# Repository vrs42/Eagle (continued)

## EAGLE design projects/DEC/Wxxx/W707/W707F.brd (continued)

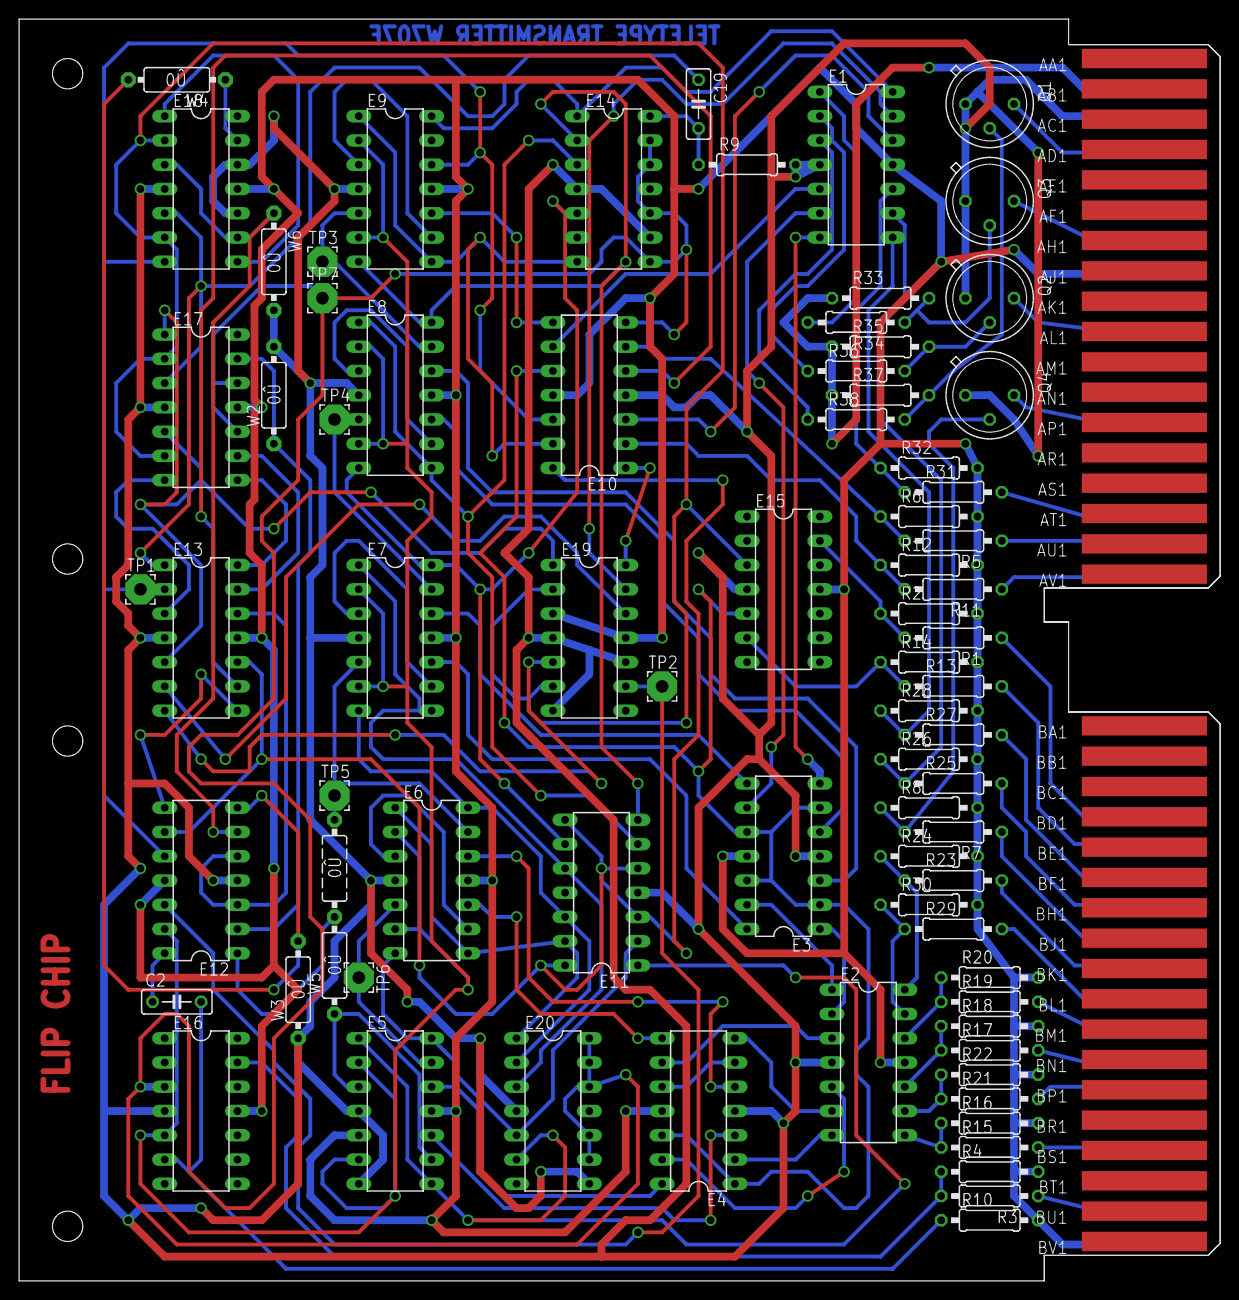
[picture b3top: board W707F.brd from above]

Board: 3 copper layers, 125.7 x 132.1 mm, 79 parts (0 on the bottom side), 110 nets.

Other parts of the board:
U$3: FLIPCHIP

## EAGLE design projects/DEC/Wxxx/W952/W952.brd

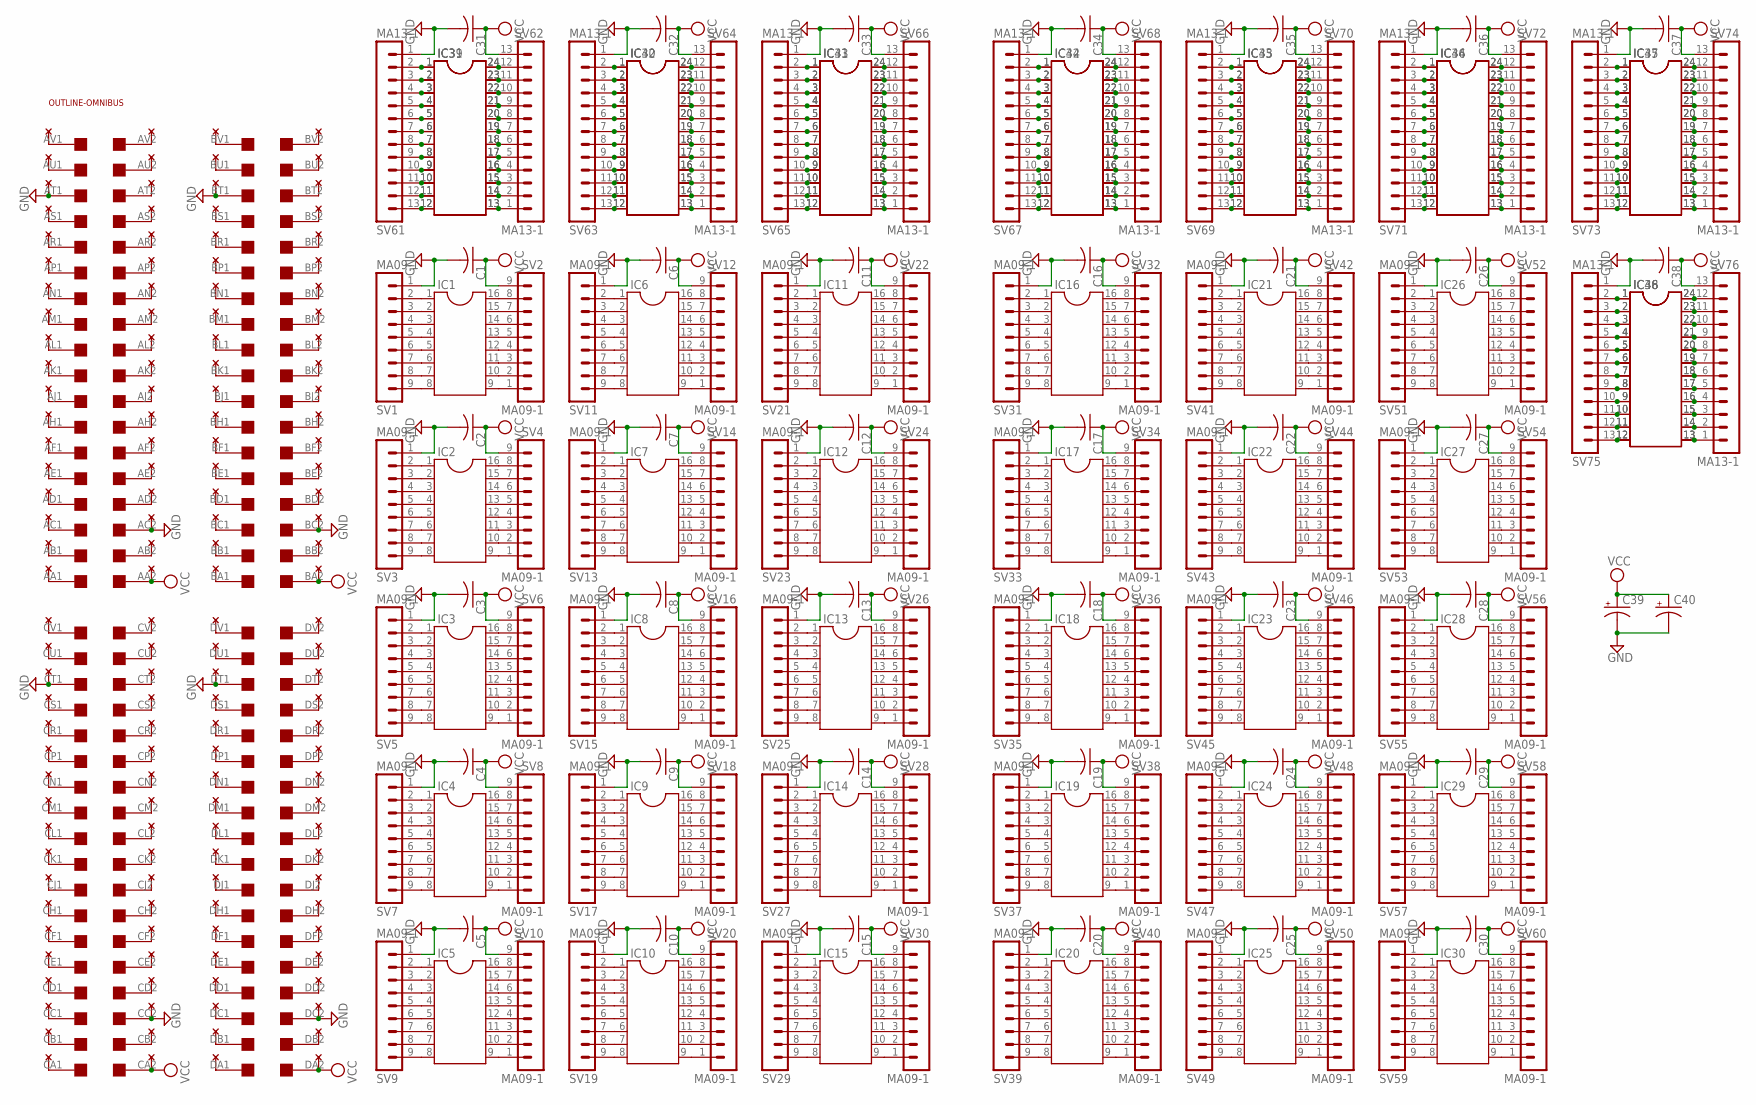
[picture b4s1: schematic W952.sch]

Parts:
C1, C2, C3, C4, C5, C6, C7, C8, C9, C10, C11, C12, C13, C14, C15, C16, C17, C18, C19, C20, C21, C22, C23, C24, C25, C26, C27, C28, C29, C30, C31, C32, C33, C34, C35, C36, C37, C38: C-US075-032X103; C075-032X103
C39, C40: CPOL-USE15-5AXIAL; E15-5
IC1, IC2, IC3, IC4, IC5, IC6, IC7, IC8, IC9, IC10, IC11, IC12, IC13, IC14, IC15, IC16, IC17, IC18, IC19, IC20, IC21, IC22, IC23, IC24, IC25, IC26, IC27, IC28, IC29, IC30: DIL16S; SOCKET-16
IC31, IC32, IC33, IC34, IC35, IC36, IC37, IC38: DIL24-6
IC39, IC40, IC41, IC42, IC43, IC44, IC45, IC46: DIL24-3
SV1, SV2, SV3, SV4, SV5, SV6, SV7, SV8, SV9, SV10, SV11, SV12, SV13, SV14, SV15, SV16, SV17, SV18, SV19, SV20, SV21, SV22, SV23, SV24, SV25, SV26, SV27, SV28, SV29, SV30, SV31, SV32, SV33, SV34, SV35, SV36, SV37, SV38, SV39, SV40, SV41, SV42, SV43, SV44, SV45, SV46, SV47, SV48, SV49, SV50, SV51, SV52, SV53, SV54, SV55, SV56, SV57, SV58, SV59, SV60: MA09-1
SV61, SV62, SV63, SV64, SV65, SV66, SV67, SV68, SV69, SV70, SV71, SV72, SV73, SV74, SV75, SV76: MA13-1
U$1: QUAD; EDGE-CON8
U$2, U$3, U$4, U$5: THRU-HOLE2W; THRU-HOLE2
U$8: OUTLINE-OMNIBUS; OMNIBUS

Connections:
GND: C1.2, C2.2, C3.2, C4.2, C5.2, C6.2, C7.2, C8.2, C9.2, C10.2, C11.2, C12.2, C13.2, C14.2, C15.2, C16.2, C17.2, C18.2, C19.2, C20.2, C21.2, C22.2, C23.2, C24.2, C25.2, C26.2, C27.2, C28.2, C29.2, C30.2, C31.2, C32.2, C33.2, C34.2, C35.2, C36.2, C37.2, C38.2, C39.-, C40.-, SV1.1, SV3.1, SV5.1, SV7.1, SV9.1, SV11.1, SV13.1, SV15.1, SV17.1, SV19.1, SV21.1, SV23.1, SV25.1, SV27.1, SV29.1, SV31.1, SV33.1, SV35.1, SV37.1, SV39.1, SV41.1, SV43.1, SV45.1, SV47.1, SV49.1, SV51.1, SV53.1, SV55.1, SV57.1, SV59.1, SV61.1, SV63.1, SV65.1, SV67.1, SV69.1, SV71.1, SV73.1, SV75.1, U$1.AC2, U$1.AT1, U$1.BC2, U$1.BT1, U$1.CC2, U$1.CT1, U$1.DC2, U$1.DT1, U$2.C1, U$2.T2, U$3.C1, U$3.T2, U$4.C1, U$4.T2, U$5.C1, U$5.T2
unnamed: U$1.AK1, U$2.K2
unnamed: U$1.AJ1, U$2.J2
unnamed: U$1.AH1, U$2.H2
unnamed: U$1.AL1, U$2.L2
unnamed: U$1.AM1, U$2.M2
unnamed: U$1.AN1, U$2.N2
unnamed: U$1.AP1, U$2.P2
unnamed: U$1.AF1, U$2.F2
unnamed: U$1.AE1, U$2.E2
unnamed: U$1.AD1, U$2.D2
unnamed: U$1.AC1, U$2.C2
unnamed: U$1.AR1, U$2.R2
unnamed: U$1.AS1, U$2.S2
unnamed: U$1.AB1, U$2.B2
unnamed: U$1.AA1, U$2.A2
unnamed: U$1.AU1, U$2.U2
unnamed: U$1.AV1, U$2.V2
unnamed: U$1.AV2, U$2.V1
unnamed: U$1.AU2, U$2.U1
unnamed: U$1.AT2, U$2.T1
unnamed: U$1.AS2, U$2.S1
unnamed: U$1.AR2, U$2.R1
unnamed: U$1.AP2, U$2.P1
unnamed: U$1.AN2, U$2.N1
unnamed: U$1.AM2, U$2.M1
unnamed: U$1.AL2, U$2.L1
unnamed: U$1.AK2, U$2.K1
unnamed: U$1.AJ2, U$2.J1
unnamed: U$1.AH2, U$2.H1
unnamed: U$1.AF2, U$2.F1
unnamed: U$1.AE2, U$2.E1
unnamed: U$1.AD2, U$2.D1
unnamed: U$1.AB2, U$2.B1
unnamed: U$1.BV1, U$3.V2
unnamed: U$1.BU1, U$3.U2
unnamed: U$1.BS1, U$3.S2
unnamed: U$1.BR1, U$3.R2
unnamed: U$1.BP1, U$3.P2
unnamed: U$1.BN1, U$3.N2
unnamed: U$1.BM1, U$3.M2
unnamed: U$1.BL1, U$3.L2
unnamed: U$1.BK1, U$3.K2
unnamed: U$1.BJ1, U$3.J2
unnamed: U$1.BH1, U$3.H2
unnamed: U$1.BF1, U$3.F2
unnamed: U$1.BE1, U$3.E2
unnamed: U$1.BD1, U$3.D2
unnamed: U$1.BC1, U$3.C2
unnamed: U$1.BB1, U$3.B2
unnamed: U$1.BA1, U$3.A2
unnamed: U$1.BV2, U$3.V1
unnamed: U$1.BU2, U$3.U1
unnamed: U$1.BT2, U$3.T1
unnamed: U$1.BS2, U$3.S1
unnamed: U$1.BR2, U$3.R1
unnamed: U$1.BP2, U$3.P1
unnamed: U$1.BN2, U$3.N1
unnamed: U$1.BM2, U$3.M1
unnamed: U$1.BL2, U$3.L1
unnamed: U$1.BK2, U$3.K1
unnamed: U$1.BJ2, U$3.J1
unnamed: U$1.BH2, U$3.H1
unnamed: U$1.BF2, U$3.F1
unnamed: U$1.BE2, U$3.E1
unnamed: U$1.BD2, U$3.D1
unnamed: U$1.BB2, U$3.B1
unnamed: U$1.CV1, U$4.V2
unnamed: U$1.CU1, U$4.U2
unnamed: U$1.CS1, U$4.S2
unnamed: U$1.CR1, U$4.R2
unnamed: U$1.CP1, U$4.P2
unnamed: U$1.CN1, U$4.N2
unnamed: U$1.CM1, U$4.M2
unnamed: U$1.CL1, U$4.L2
unnamed: U$1.CK1, U$4.K2
unnamed: U$1.CJ1, U$4.J2
unnamed: U$1.CH1, U$4.H2
unnamed: U$1.CF1, U$4.F2
unnamed: U$1.CE1, U$4.E2
unnamed: U$1.CD1, U$4.D2
unnamed: U$1.CC1, U$4.C2
unnamed: U$1.CB1, U$4.B2
unnamed: U$1.CA1, U$4.A2
unnamed: U$1.CV2, U$4.V1
unnamed: U$1.CU2, U$4.U1
unnamed: U$1.CT2, U$4.T1
unnamed: U$1.CS2, U$4.S1
unnamed: U$1.CR2, U$4.R1
unnamed: U$1.CP2, U$4.P1
unnamed: U$1.CN2, U$4.N1
unnamed: U$1.CM2, U$4.M1
unnamed: U$1.CL2, U$4.L1
unnamed: U$1.CK2, U$4.K1
unnamed: U$1.CJ2, U$4.J1
unnamed: U$1.CH2, U$4.H1
unnamed: U$1.CF2, U$4.F1
unnamed: U$1.CE2, U$4.E1
unnamed: U$1.CD2, U$4.D1
unnamed: U$1.CB2, U$4.B1
unnamed: U$1.DV1, U$5.V2
unnamed: U$1.DU1, U$5.U2
unnamed: U$1.DS1, U$5.S2
unnamed: U$1.DR1, U$5.R2
unnamed: U$1.DP1, U$5.P2
unnamed: U$1.DN1, U$5.N2
unnamed: U$1.DM1, U$5.M2
unnamed: U$1.DL1, U$5.L2
unnamed: U$1.DK1, U$5.K2
unnamed: U$1.DJ1, U$5.J2
unnamed: U$1.DH1, U$5.H2
unnamed: U$1.DF1, U$5.F2
unnamed: U$1.DE1, U$5.E2
unnamed: U$1.DD1, U$5.D2
unnamed: U$1.DC1, U$5.C2
unnamed: U$1.DB1, U$5.B2
unnamed: U$1.DA1, U$5.A2
unnamed: U$1.DV2, U$5.V1
unnamed: U$1.DU2, U$5.U1
unnamed: U$1.DT2, U$5.T1
unnamed: U$1.DS2, U$5.S1
unnamed: U$1.DR2, U$5.R1
unnamed: U$1.DP2, U$5.P1
unnamed: U$1.DN2, U$5.N1
unnamed: U$1.DM2, U$5.M1
unnamed: U$1.DL2, U$5.L1
unnamed: U$1.DK2, U$5.K1
unnamed: U$1.DJ2, U$5.J1
unnamed: U$1.DH2, U$5.H1
unnamed: U$1.DF2, U$5.F1
unnamed: U$1.DE2, U$5.E1
unnamed: U$1.DD2, U$5.D1
unnamed: U$1.DB2, U$5.B1
unnamed: IC1.1, SV1.2
unnamed: IC1.2, SV1.3
unnamed: IC1.3, SV1.4
unnamed: IC1.4, SV1.5
unnamed: IC1.5, SV1.6
unnamed: IC1.6, SV1.7
unnamed: IC1.7, SV1.8
unnamed: IC1.8, SV1.9
unnamed: IC1.9, SV2.1
unnamed: IC1.10, SV2.2
unnamed: IC1.11, SV2.3
unnamed: IC1.12, SV2.4
unnamed: IC1.13, SV2.5
unnamed: IC1.14, SV2.6
unnamed: IC1.15, SV2.7
unnamed: IC1.16, SV2.8
unnamed: IC2.1, SV3.2
unnamed: IC2.2, SV3.3
unnamed: IC2.3, SV3.4
unnamed: IC2.4, SV3.5
unnamed: IC2.5, SV3.6
unnamed: IC2.6, SV3.7
unnamed: IC2.7, SV3.8
unnamed: IC2.8, SV3.9
unnamed: IC2.9, SV4.1
unnamed: IC2.10, SV4.2
unnamed: IC2.11, SV4.3
unnamed: IC2.12, SV4.4
unnamed: IC2.13, SV4.5
unnamed: IC2.14, SV4.6
unnamed: IC2.15, SV4.7
unnamed: IC2.16, SV4.8
unnamed: IC3.1, SV5.2
unnamed: IC3.2, SV5.3
unnamed: IC3.3, SV5.4
unnamed: IC3.4, SV5.5
unnamed: IC3.5, SV5.6
unnamed: IC3.6, SV5.7
unnamed: IC3.7, SV5.8
unnamed: IC3.8, SV5.9
unnamed: IC3.9, SV6.1
unnamed: IC3.10, SV6.2
unnamed: IC3.11, SV6.3
unnamed: IC3.12, SV6.4
unnamed: IC3.13, SV6.5
unnamed: IC3.14, SV6.6
unnamed: IC3.15, SV6.7
unnamed: IC3.16, SV6.8
unnamed: IC4.1, SV7.2
unnamed: IC4.2, SV7.3
unnamed: IC4.3, SV7.4
unnamed: IC4.4, SV7.5
unnamed: IC4.5, SV7.6
unnamed: IC4.6, SV7.7
unnamed: IC4.7, SV7.8
unnamed: IC4.8, SV7.9
unnamed: IC4.9, SV8.1
unnamed: IC4.10, SV8.2
unnamed: IC4.11, SV8.3
unnamed: IC4.12, SV8.4
unnamed: IC4.13, SV8.5
unnamed: IC4.14, SV8.6
unnamed: IC4.15, SV8.7
unnamed: IC4.16, SV8.8
unnamed: IC5.1, SV9.2
unnamed: IC5.2, SV9.3
unnamed: IC5.3, SV9.4
unnamed: IC5.4, SV9.5
unnamed: IC5.5, SV9.6
unnamed: IC5.6, SV9.7
unnamed: IC5.7, SV9.8
unnamed: IC5.8, SV9.9
unnamed: IC5.9, SV10.1
unnamed: IC5.10, SV10.2
unnamed: IC5.11, SV10.3
unnamed: IC5.12, SV10.4
unnamed: IC5.13, SV10.5
unnamed: IC5.14, SV10.6
unnamed: IC5.15, SV10.7
unnamed: IC5.16, SV10.8
unnamed: IC6.1, SV11.2
unnamed: IC6.2, SV11.3
unnamed: IC6.3, SV11.4
unnamed: IC6.4, SV11.5
unnamed: IC6.5, SV11.6
unnamed: IC6.6, SV11.7
unnamed: IC6.7, SV11.8
unnamed: IC6.8, SV11.9
unnamed: IC6.9, SV12.1
unnamed: IC6.10, SV12.2
unnamed: IC6.11, SV12.3
unnamed: IC6.12, SV12.4
unnamed: IC6.13, SV12.5
unnamed: IC6.14, SV12.6
unnamed: IC6.15, SV12.7
unnamed: IC6.16, SV12.8
unnamed: IC7.1, SV13.2
unnamed: IC7.2, SV13.3
unnamed: IC7.3, SV13.4
unnamed: IC7.4, SV13.5
unnamed: IC7.5, SV13.6
unnamed: IC7.6, SV13.7
unnamed: IC7.7, SV13.8
unnamed: IC7.8, SV13.9
unnamed: IC7.9, SV14.1
unnamed: IC7.10, SV14.2
unnamed: IC7.11, SV14.3
unnamed: IC7.12, SV14.4
unnamed: IC7.13, SV14.5
unnamed: IC7.14, SV14.6
unnamed: IC7.15, SV14.7
unnamed: IC7.16, SV14.8
unnamed: IC8.1, SV15.2
unnamed: IC8.2, SV15.3
unnamed: IC8.3, SV15.4
unnamed: IC8.4, SV15.5
unnamed: IC8.5, SV15.6
unnamed: IC8.6, SV15.7
unnamed: IC8.7, SV15.8
unnamed: IC8.8, SV15.9
unnamed: IC8.9, SV16.1
unnamed: IC8.10, SV16.2
unnamed: IC8.11, SV16.3
unnamed: IC8.12, SV16.4
unnamed: IC8.13, SV16.5
unnamed: IC8.14, SV16.6
unnamed: IC8.15, SV16.7
unnamed: IC8.16, SV16.8
unnamed: IC9.1, SV17.2
unnamed: IC9.2, SV17.3
unnamed: IC9.3, SV17.4
unnamed: IC9.4, SV17.5
unnamed: IC9.5, SV17.6
unnamed: IC9.6, SV17.7
unnamed: IC9.7, SV17.8
unnamed: IC9.8, SV17.9
unnamed: IC9.9, SV18.1
unnamed: IC9.10, SV18.2
unnamed: IC9.11, SV18.3
unnamed: IC9.12, SV18.4
unnamed: IC9.13, SV18.5
unnamed: IC9.14, SV18.6
unnamed: IC9.15, SV18.7
unnamed: IC9.16, SV18.8
unnamed: IC10.1, SV19.2
unnamed: IC10.2, SV19.3
unnamed: IC10.3, SV19.4
unnamed: IC10.4, SV19.5
unnamed: IC10.5, SV19.6
unnamed: IC10.6, SV19.7
unnamed: IC10.7, SV19.8
unnamed: IC10.8, SV19.9
unnamed: IC10.9, SV20.1
unnamed: IC10.10, SV20.2
unnamed: IC10.11, SV20.3
unnamed: IC10.12, SV20.4
unnamed: IC10.13, SV20.5
unnamed: IC10.14, SV20.6
unnamed: IC10.15, SV20.7
unnamed: IC10.16, SV20.8
unnamed: IC11.1, SV21.2
unnamed: IC11.2, SV21.3
unnamed: IC11.3, SV21.4
unnamed: IC11.4, SV21.5
unnamed: IC11.5, SV21.6
unnamed: IC11.6, SV21.7
unnamed: IC11.7, SV21.8
unnamed: IC11.8, SV21.9
unnamed: IC11.9, SV22.1
unnamed: IC11.10, SV22.2
unnamed: IC11.11, SV22.3
unnamed: IC11.12, SV22.4
unnamed: IC11.13, SV22.5
unnamed: IC11.14, SV22.6
unnamed: IC11.15, SV22.7
unnamed: IC11.16, SV22.8
unnamed: IC12.1, SV23.2
unnamed: IC12.2, SV23.3
unnamed: IC12.3, SV23.4
unnamed: IC12.4, SV23.5
unnamed: IC12.5, SV23.6
unnamed: IC12.6, SV23.7
unnamed: IC12.7, SV23.8
unnamed: IC12.8, SV23.9
unnamed: IC12.9, SV24.1
unnamed: IC12.10, SV24.2
unnamed: IC12.11, SV24.3
unnamed: IC12.12, SV24.4
unnamed: IC12.13, SV24.5
unnamed: IC12.14, SV24.6
unnamed: IC12.15, SV24.7
unnamed: IC12.16, SV24.8
unnamed: IC13.1, SV25.2
unnamed: IC13.2, SV25.3
unnamed: IC13.3, SV25.4
unnamed: IC13.4, SV25.5
unnamed: IC13.5, SV25.6
unnamed: IC13.6, SV25.7
unnamed: IC13.7, SV25.8
unnamed: IC13.8, SV25.9
unnamed: IC13.9, SV26.1
unnamed: IC13.10, SV26.2
unnamed: IC13.11, SV26.3
unnamed: IC13.12, SV26.4
unnamed: IC13.13, SV26.5
unnamed: IC13.14, SV26.6
unnamed: IC13.15, SV26.7
unnamed: IC13.16, SV26.8
unnamed: IC14.1, SV27.2
unnamed: IC14.2, SV27.3
unnamed: IC14.3, SV27.4
unnamed: IC14.4, SV27.5
unnamed: IC14.5, SV27.6
unnamed: IC14.6, SV27.7
unnamed: IC14.7, SV27.8
unnamed: IC14.8, SV27.9
unnamed: IC14.9, SV28.1
unnamed: IC14.10, SV28.2
unnamed: IC14.11, SV28.3
unnamed: IC14.12, SV28.4
unnamed: IC14.13, SV28.5
unnamed: IC14.14, SV28.6
unnamed: IC14.15, SV28.7
unnamed: IC14.16, SV28.8
unnamed: IC15.1, SV29.2
unnamed: IC15.2, SV29.3
unnamed: IC15.3, SV29.4
unnamed: IC15.4, SV29.5
unnamed: IC15.5, SV29.6
unnamed: IC15.6, SV29.7
unnamed: IC15.7, SV29.8
unnamed: IC15.8, SV29.9
unnamed: IC15.9, SV30.1
unnamed: IC15.10, SV30.2
unnamed: IC15.11, SV30.3
unnamed: IC15.12, SV30.4
unnamed: IC15.13, SV30.5
unnamed: IC15.14, SV30.6
unnamed: IC15.15, SV30.7
unnamed: IC15.16, SV30.8
unnamed: IC16.1, SV31.2
unnamed: IC16.2, SV31.3
unnamed: IC16.3, SV31.4
unnamed: IC16.4, SV31.5
unnamed: IC16.5, SV31.6
unnamed: IC16.6, SV31.7
unnamed: IC16.7, SV31.8
unnamed: IC16.8, SV31.9
unnamed: IC16.9, SV32.1
unnamed: IC16.10, SV32.2
unnamed: IC16.11, SV32.3
unnamed: IC16.12, SV32.4
unnamed: IC16.13, SV32.5
unnamed: IC16.14, SV32.6
unnamed: IC16.15, SV32.7
unnamed: IC16.16, SV32.8
unnamed: IC17.1, SV33.2
unnamed: IC17.2, SV33.3
unnamed: IC17.3, SV33.4
unnamed: IC17.4, SV33.5
unnamed: IC17.5, SV33.6
unnamed: IC17.6, SV33.7
unnamed: IC17.7, SV33.8
unnamed: IC17.8, SV33.9
unnamed: IC17.9, SV34.1
unnamed: IC17.10, SV34.2
unnamed: IC17.11, SV34.3
unnamed: IC17.12, SV34.4
unnamed: IC17.13, SV34.5
unnamed: IC17.14, SV34.6
unnamed: IC17.15, SV34.7
unnamed: IC17.16, SV34.8
unnamed: IC18.1, SV35.2
unnamed: IC18.2, SV35.3
unnamed: IC18.3, SV35.4
unnamed: IC18.4, SV35.5
unnamed: IC18.5, SV35.6
unnamed: IC18.6, SV35.7
unnamed: IC18.7, SV35.8
unnamed: IC18.8, SV35.9
unnamed: IC18.9, SV36.1
unnamed: IC18.10, SV36.2
unnamed: IC18.11, SV36.3
unnamed: IC18.12, SV36.4
unnamed: IC18.13, SV36.5
unnamed: IC18.14, SV36.6
unnamed: IC18.15, SV36.7
unnamed: IC18.16, SV36.8
unnamed: IC19.1, SV37.2
unnamed: IC19.2, SV37.3
unnamed: IC19.3, SV37.4
unnamed: IC19.4, SV37.5
unnamed: IC19.5, SV37.6
unnamed: IC19.6, SV37.7
unnamed: IC19.7, SV37.8
unnamed: IC19.8, SV37.9
unnamed: IC19.9, SV38.1
unnamed: IC19.10, SV38.2
unnamed: IC19.11, SV38.3
unnamed: IC19.12, SV38.4
unnamed: IC19.13, SV38.5
unnamed: IC19.14, SV38.6
unnamed: IC19.15, SV38.7
unnamed: IC19.16, SV38.8
unnamed: IC20.1, SV39.2
unnamed: IC20.2, SV39.3
unnamed: IC20.3, SV39.4
unnamed: IC20.4, SV39.5
unnamed: IC20.5, SV39.6
unnamed: IC20.6, SV39.7
unnamed: IC20.7, SV39.8
unnamed: IC20.8, SV39.9
unnamed: IC20.9, SV40.1
unnamed: IC20.10, SV40.2
unnamed: IC20.11, SV40.3
unnamed: IC20.12, SV40.4
unnamed: IC20.13, SV40.5
unnamed: IC20.14, SV40.6
unnamed: IC20.15, SV40.7
unnamed: IC20.16, SV40.8
unnamed: IC21.1, SV41.2
unnamed: IC21.2, SV41.3
unnamed: IC21.3, SV41.4
unnamed: IC21.4, SV41.5
unnamed: IC21.5, SV41.6
unnamed: IC21.6, SV41.7
unnamed: IC21.7, SV41.8
unnamed: IC21.8, SV41.9
unnamed: IC21.9, SV42.1
unnamed: IC21.10, SV42.2
unnamed: IC21.11, SV42.3
unnamed: IC21.12, SV42.4
unnamed: IC21.13, SV42.5
unnamed: IC21.14, SV42.6
unnamed: IC21.15, SV42.7
unnamed: IC21.16, SV42.8
unnamed: IC22.1, SV43.2
unnamed: IC22.2, SV43.3
unnamed: IC22.3, SV43.4
unnamed: IC22.4, SV43.5
unnamed: IC22.5, SV43.6
unnamed: IC22.6, SV43.7
unnamed: IC22.7, SV43.8
unnamed: IC22.8, SV43.9
unnamed: IC22.9, SV44.1
unnamed: IC22.10, SV44.2
unnamed: IC22.11, SV44.3
unnamed: IC22.12, SV44.4
unnamed: IC22.13, SV44.5
unnamed: IC22.14, SV44.6
unnamed: IC22.15, SV44.7
unnamed: IC22.16, SV44.8
unnamed: IC23.1, SV45.2
unnamed: IC23.2, SV45.3
unnamed: IC23.3, SV45.4
unnamed: IC23.4, SV45.5
unnamed: IC23.5, SV45.6
unnamed: IC23.6, SV45.7
unnamed: IC23.7, SV45.8
unnamed: IC23.8, SV45.9
unnamed: IC23.9, SV46.1
unnamed: IC23.10, SV46.2
unnamed: IC23.11, SV46.3
unnamed: IC23.12, SV46.4
unnamed: IC23.13, SV46.5
unnamed: IC23.14, SV46.6
unnamed: IC23.15, SV46.7
unnamed: IC23.16, SV46.8
unnamed: IC24.1, SV47.2
unnamed: IC24.2, SV47.3
unnamed: IC24.3, SV47.4
unnamed: IC24.4, SV47.5
unnamed: IC24.5, SV47.6
unnamed: IC24.6, SV47.7
unnamed: IC24.7, SV47.8
unnamed: IC24.8, SV47.9
unnamed: IC24.9, SV48.1
unnamed: IC24.10, SV48.2
unnamed: IC24.11, SV48.3
unnamed: IC24.12, SV48.4
unnamed: IC24.13, SV48.5
unnamed: IC24.14, SV48.6
unnamed: IC24.15, SV48.7
unnamed: IC24.16, SV48.8
unnamed: IC25.1, SV49.2
unnamed: IC25.2, SV49.3
unnamed: IC25.3, SV49.4
unnamed: IC25.4, SV49.5
unnamed: IC25.5, SV49.6
unnamed: IC25.6, SV49.7
unnamed: IC25.7, SV49.8
unnamed: IC25.8, SV49.9
unnamed: IC25.9, SV50.1
unnamed: IC25.10, SV50.2
unnamed: IC25.11, SV50.3
unnamed: IC25.12, SV50.4
unnamed: IC25.13, SV50.5
unnamed: IC25.14, SV50.6
unnamed: IC25.15, SV50.7
unnamed: IC25.16, SV50.8
unnamed: IC26.1, SV51.2
unnamed: IC26.2, SV51.3
unnamed: IC26.3, SV51.4
unnamed: IC26.4, SV51.5
unnamed: IC26.5, SV51.6
unnamed: IC26.6, SV51.7
unnamed: IC26.7, SV51.8
unnamed: IC26.8, SV51.9
unnamed: IC26.9, SV52.1
unnamed: IC26.10, SV52.2
unnamed: IC26.11, SV52.3
unnamed: IC26.12, SV52.4
unnamed: IC26.13, SV52.5
unnamed: IC26.14, SV52.6
unnamed: IC26.15, SV52.7
unnamed: IC26.16, SV52.8
unnamed: IC27.1, SV53.2
unnamed: IC27.2, SV53.3
unnamed: IC27.3, SV53.4
unnamed: IC27.4, SV53.5
unnamed: IC27.5, SV53.6
unnamed: IC27.6, SV53.7
unnamed: IC27.7, SV53.8
unnamed: IC27.8, SV53.9
unnamed: IC27.9, SV54.1
unnamed: IC27.10, SV54.2
unnamed: IC27.11, SV54.3
unnamed: IC27.12, SV54.4
unnamed: IC27.13, SV54.5
unnamed: IC27.14, SV54.6
unnamed: IC27.15, SV54.7
unnamed: IC27.16, SV54.8
unnamed: IC28.1, SV55.2
unnamed: IC28.2, SV55.3
unnamed: IC28.3, SV55.4
unnamed: IC28.4, SV55.5
unnamed: IC28.5, SV55.6
unnamed: IC28.6, SV55.7
unnamed: IC28.7, SV55.8
unnamed: IC28.8, SV55.9
unnamed: IC28.9, SV56.1
unnamed: IC28.10, SV56.2
unnamed: IC28.11, SV56.3
unnamed: IC28.12, SV56.4
unnamed: IC28.13, SV56.5
unnamed: IC28.14, SV56.6
unnamed: IC28.15, SV56.7
unnamed: IC28.16, SV56.8
unnamed: IC29.1, SV57.2
unnamed: IC29.2, SV57.3
unnamed: IC29.3, SV57.4
unnamed: IC29.4, SV57.5
unnamed: IC29.5, SV57.6
unnamed: IC29.6, SV57.7
unnamed: IC29.7, SV57.8
unnamed: IC29.8, SV57.9
unnamed: IC29.9, SV58.1
unnamed: IC29.10, SV58.2
unnamed: IC29.11, SV58.3
unnamed: IC29.12, SV58.4
unnamed: IC29.13, SV58.5
unnamed: IC29.14, SV58.6
unnamed: IC29.15, SV58.7
unnamed: IC29.16, SV58.8
unnamed: IC30.1, SV59.2
unnamed: IC30.2, SV59.3
unnamed: IC30.3, SV59.4
unnamed: IC30.4, SV59.5
unnamed: IC30.5, SV59.6
unnamed: IC30.6, SV59.7
unnamed: IC30.7, SV59.8
unnamed: IC30.8, SV59.9
unnamed: IC30.9, SV60.1
unnamed: IC30.10, SV60.2
unnamed: IC30.11, SV60.3
unnamed: IC30.12, SV60.4
unnamed: IC30.13, SV60.5
unnamed: IC30.14, SV60.6
unnamed: IC30.15, SV60.7
unnamed: IC30.16, SV60.8
unnamed: IC31.1, IC39.1, SV61.2
unnamed: IC31.2, IC39.2, SV61.3
unnamed: IC31.3, IC39.3, SV61.4
unnamed: IC31.4, IC39.4, SV61.5
unnamed: IC31.5, IC39.5, SV61.6
unnamed: IC31.6, IC39.6, SV61.7
unnamed: IC31.7, IC39.7, SV61.8
unnamed: IC31.8, IC39.8, SV61.9
unnamed: IC31.9, IC39.9, SV61.10
unnamed: IC31.10, IC39.10, SV61.11
unnamed: IC31.11, IC39.11, SV61.12
unnamed: IC31.12, IC39.12, SV61.13
unnamed: IC31.13, IC39.13, SV62.1
unnamed: IC31.14, IC39.14, SV62.2
unnamed: IC31.15, IC39.15, SV62.3
unnamed: IC31.16, IC39.16, SV62.4
unnamed: IC31.17, IC39.17, SV62.5
unnamed: IC31.18, IC39.18, SV62.6
unnamed: IC31.19, IC39.19, SV62.7
unnamed: IC31.20, IC39.20, SV62.8
unnamed: IC31.21, IC39.21, SV62.9
unnamed: IC31.22, IC39.22, SV62.10
unnamed: IC31.23, IC39.23, SV62.11
unnamed: IC31.24, IC39.24, SV62.12
unnamed: IC32.1, IC40.1, SV63.2
unnamed: IC32.2, IC40.2, SV63.3
unnamed: IC32.3, IC40.3, SV63.4
unnamed: IC32.4, IC40.4, SV63.5
unnamed: IC32.5, IC40.5, SV63.6
unnamed: IC32.6, IC40.6, SV63.7
unnamed: IC32.7, IC40.7, SV63.8
unnamed: IC32.8, IC40.8, SV63.9
unnamed: IC32.9, IC40.9, SV63.10
unnamed: IC32.10, IC40.10, SV63.11
unnamed: IC32.11, IC40.11, SV63.12
unnamed: IC32.12, IC40.12, SV63.13
unnamed: IC32.13, IC40.13, SV64.1
unnamed: IC32.14, IC40.14, SV64.2
unnamed: IC32.15, IC40.15, SV64.3
unnamed: IC32.16, IC40.16, SV64.4
unnamed: IC32.17, IC40.17, SV64.5
unnamed: IC32.18, IC40.18, SV64.6
unnamed: IC32.19, IC40.19, SV64.7
unnamed: IC32.20, IC40.20, SV64.8
unnamed: IC32.21, IC40.21, SV64.9
unnamed: IC32.22, IC40.22, SV64.10
unnamed: IC32.23, IC40.23, SV64.11
unnamed: IC32.24, IC40.24, SV64.12
unnamed: IC33.1, IC41.1, SV65.2
unnamed: IC33.2, IC41.2, SV65.3
unnamed: IC33.3, IC41.3, SV65.4
unnamed: IC33.4, IC41.4, SV65.5
unnamed: IC33.5, IC41.5, SV65.6
unnamed: IC33.6, IC41.6, SV65.7
unnamed: IC33.7, IC41.7, SV65.8
unnamed: IC33.8, IC41.8, SV65.9
unnamed: IC33.9, IC41.9, SV65.10
unnamed: IC33.10, IC41.10, SV65.11
unnamed: IC33.11, IC41.11, SV65.12
unnamed: IC33.12, IC41.12, SV65.13
unnamed: IC33.13, IC41.13, SV66.1
unnamed: IC33.14, IC41.14, SV66.2
unnamed: IC33.15, IC41.15, SV66.3
unnamed: IC33.16, IC41.16, SV66.4
unnamed: IC33.17, IC41.17, SV66.5
unnamed: IC33.18, IC41.18, SV66.6
unnamed: IC33.19, IC41.19, SV66.7
unnamed: IC33.20, IC41.20, SV66.8
unnamed: IC33.21, IC41.21, SV66.9
unnamed: IC33.22, IC41.22, SV66.10
unnamed: IC33.23, IC41.23, SV66.11
unnamed: IC33.24, IC41.24, SV66.12
unnamed: IC34.1, IC42.1, SV67.2
unnamed: IC34.2, IC42.2, SV67.3
unnamed: IC34.3, IC42.3, SV67.4
unnamed: IC34.4, IC42.4, SV67.5
unnamed: IC34.5, IC42.5, SV67.6
unnamed: IC34.6, IC42.6, SV67.7
unnamed: IC34.7, IC42.7, SV67.8
unnamed: IC34.8, IC42.8, SV67.9
unnamed: IC34.9, IC42.9, SV67.10
unnamed: IC34.10, IC42.10, SV67.11
unnamed: IC34.11, IC42.11, SV67.12
unnamed: IC34.12, IC42.12, SV67.13
unnamed: IC34.13, IC42.13, SV68.1
unnamed: IC34.14, IC42.14, SV68.2
unnamed: IC34.15, IC42.15, SV68.3
unnamed: IC34.16, IC42.16, SV68.4
unnamed: IC34.17, IC42.17, SV68.5
unnamed: IC34.18, IC42.18, SV68.6
unnamed: IC34.19, IC42.19, SV68.7
unnamed: IC34.20, IC42.20, SV68.8
unnamed: IC34.21, IC42.21, SV68.9
unnamed: IC34.22, IC42.22, SV68.10
unnamed: IC34.23, IC42.23, SV68.11
unnamed: IC34.24, IC42.24, SV68.12
unnamed: IC35.1, IC43.1, SV69.2
unnamed: IC35.2, IC43.2, SV69.3
unnamed: IC35.3, IC43.3, SV69.4
unnamed: IC35.4, IC43.4, SV69.5
unnamed: IC35.5, IC43.5, SV69.6
unnamed: IC35.6, IC43.6, SV69.7
unnamed: IC35.7, IC43.7, SV69.8
unnamed: IC35.8, IC43.8, SV69.9
unnamed: IC35.9, IC43.9, SV69.10
unnamed: IC35.10, IC43.10, SV69.11
unnamed: IC35.11, IC43.11, SV69.12
unnamed: IC35.12, IC43.12, SV69.13
unnamed: IC35.13, IC43.13, SV70.1
unnamed: IC35.14, IC43.14, SV70.2
unnamed: IC35.15, IC43.15, SV70.3
unnamed: IC35.16, IC43.16, SV70.4
unnamed: IC35.17, IC43.17, SV70.5
unnamed: IC35.18, IC43.18, SV70.6
unnamed: IC35.19, IC43.19, SV70.7
unnamed: IC35.20, IC43.20, SV70.8
unnamed: IC35.21, IC43.21, SV70.9
unnamed: IC35.22, IC43.22, SV70.10
unnamed: IC35.23, IC43.23, SV70.11
unnamed: IC35.24, IC43.24, SV70.12
unnamed: IC36.1, IC44.1, SV71.2
unnamed: IC36.2, IC44.2, SV71.3
unnamed: IC36.3, IC44.3, SV71.4
unnamed: IC36.4, IC44.4, SV71.5
unnamed: IC36.5, IC44.5, SV71.6
unnamed: IC36.6, IC44.6, SV71.7
unnamed: IC36.7, IC44.7, SV71.8
unnamed: IC36.8, IC44.8, SV71.9
unnamed: IC36.9, IC44.9, SV71.10
unnamed: IC36.10, IC44.10, SV71.11
unnamed: IC36.11, IC44.11, SV71.12
unnamed: IC36.12, IC44.12, SV71.13
unnamed: IC36.13, IC44.13, SV72.1
unnamed: IC36.14, IC44.14, SV72.2
unnamed: IC36.15, IC44.15, SV72.3
unnamed: IC36.16, IC44.16, SV72.4
unnamed: IC36.17, IC44.17, SV72.5
unnamed: IC36.18, IC44.18, SV72.6
unnamed: IC36.19, IC44.19, SV72.7
unnamed: IC36.20, IC44.20, SV72.8
unnamed: IC36.21, IC44.21, SV72.9
unnamed: IC36.22, IC44.22, SV72.10
unnamed: IC36.23, IC44.23, SV72.11
unnamed: IC36.24, IC44.24, SV72.12
unnamed: IC37.1, IC45.1, SV73.2
unnamed: IC37.2, IC45.2, SV73.3
unnamed: IC37.3, IC45.3, SV73.4
unnamed: IC37.4, IC45.4, SV73.5
unnamed: IC37.5, IC45.5, SV73.6
unnamed: IC37.6, IC45.6, SV73.7
unnamed: IC37.7, IC45.7, SV73.8
unnamed: IC37.8, IC45.8, SV73.9
unnamed: IC37.9, IC45.9, SV73.10
unnamed: IC37.10, IC45.10, SV73.11
unnamed: IC37.11, IC45.11, SV73.12
unnamed: IC37.12, IC45.12, SV73.13
unnamed: IC37.13, IC45.13, SV74.1
unnamed: IC37.14, IC45.14, SV74.2
unnamed: IC37.15, IC45.15, SV74.3
unnamed: IC37.16, IC45.16, SV74.4
unnamed: IC37.17, IC45.17, SV74.5
unnamed: IC37.18, IC45.18, SV74.6
unnamed: IC37.19, IC45.19, SV74.7
unnamed: IC37.20, IC45.20, SV74.8
unnamed: IC37.21, IC45.21, SV74.9
unnamed: IC37.22, IC45.22, SV74.10
unnamed: IC37.23, IC45.23, SV74.11
unnamed: IC37.24, IC45.24, SV74.12
unnamed: IC38.1, IC46.1, SV75.2
unnamed: IC38.2, IC46.2, SV75.3
unnamed: IC38.3, IC46.3, SV75.4
unnamed: IC38.4, IC46.4, SV75.5
unnamed: IC38.5, IC46.5, SV75.6
unnamed: IC38.6, IC46.6, SV75.7
unnamed: IC38.7, IC46.7, SV75.8
unnamed: IC38.8, IC46.8, SV75.9
unnamed: IC38.9, IC46.9, SV75.10
unnamed: IC38.10, IC46.10, SV75.11
unnamed: IC38.11, IC46.11, SV75.12
unnamed: IC38.12, IC46.12, SV75.13
unnamed: IC38.13, IC46.13, SV76.1
unnamed: IC38.14, IC46.14, SV76.2
unnamed: IC38.15, IC46.15, SV76.3
unnamed: IC38.16, IC46.16, SV76.4
unnamed: IC38.17, IC46.17, SV76.5
unnamed: IC38.18, IC46.18, SV76.6
unnamed: IC38.19, IC46.19, SV76.7
unnamed: IC38.20, IC46.20, SV76.8
unnamed: IC38.21, IC46.21, SV76.9
unnamed: IC38.22, IC46.22, SV76.10
unnamed: IC38.23, IC46.23, SV76.11
unnamed: IC38.24, IC46.24, SV76.12
VCC: C1.1, C2.1, C3.1, C4.1, C5.1, C6.1, C7.1, C8.1, C9.1, C10.1, C11.1, C12.1, C13.1, C14.1, C15.1, C16.1, C17.1, C18.1, C19.1, C20.1, C21.1, C22.1, C23.1, C24.1, C25.1, C26.1, C27.1, C28.1, C29.1, C30.1, C31.1, C32.1, C33.1, C34.1, C35.1, C36.1, C37.1, C38.1, C39.+, C40.+, SV2.9, SV4.9, SV6.9, SV8.9, SV10.9, SV12.9, SV14.9, SV16.9, SV18.9, SV20.9, SV22.9, SV24.9, SV26.9, SV28.9, SV30.9, SV32.9, SV34.9, SV36.9, SV38.9, SV40.9, SV42.9, SV44.9, SV46.9, SV48.9, SV50.9, SV52.9, SV54.9, SV56.9, SV58.9, SV60.9, SV62.13, SV64.13, SV66.13, SV68.13, SV70.13, SV72.13, SV74.13, SV76.13, U$1.AA2, U$1.BA2, U$1.CA2, U$1.DA2, U$2.A1, U$3.A1, U$4.A1, U$5.A1

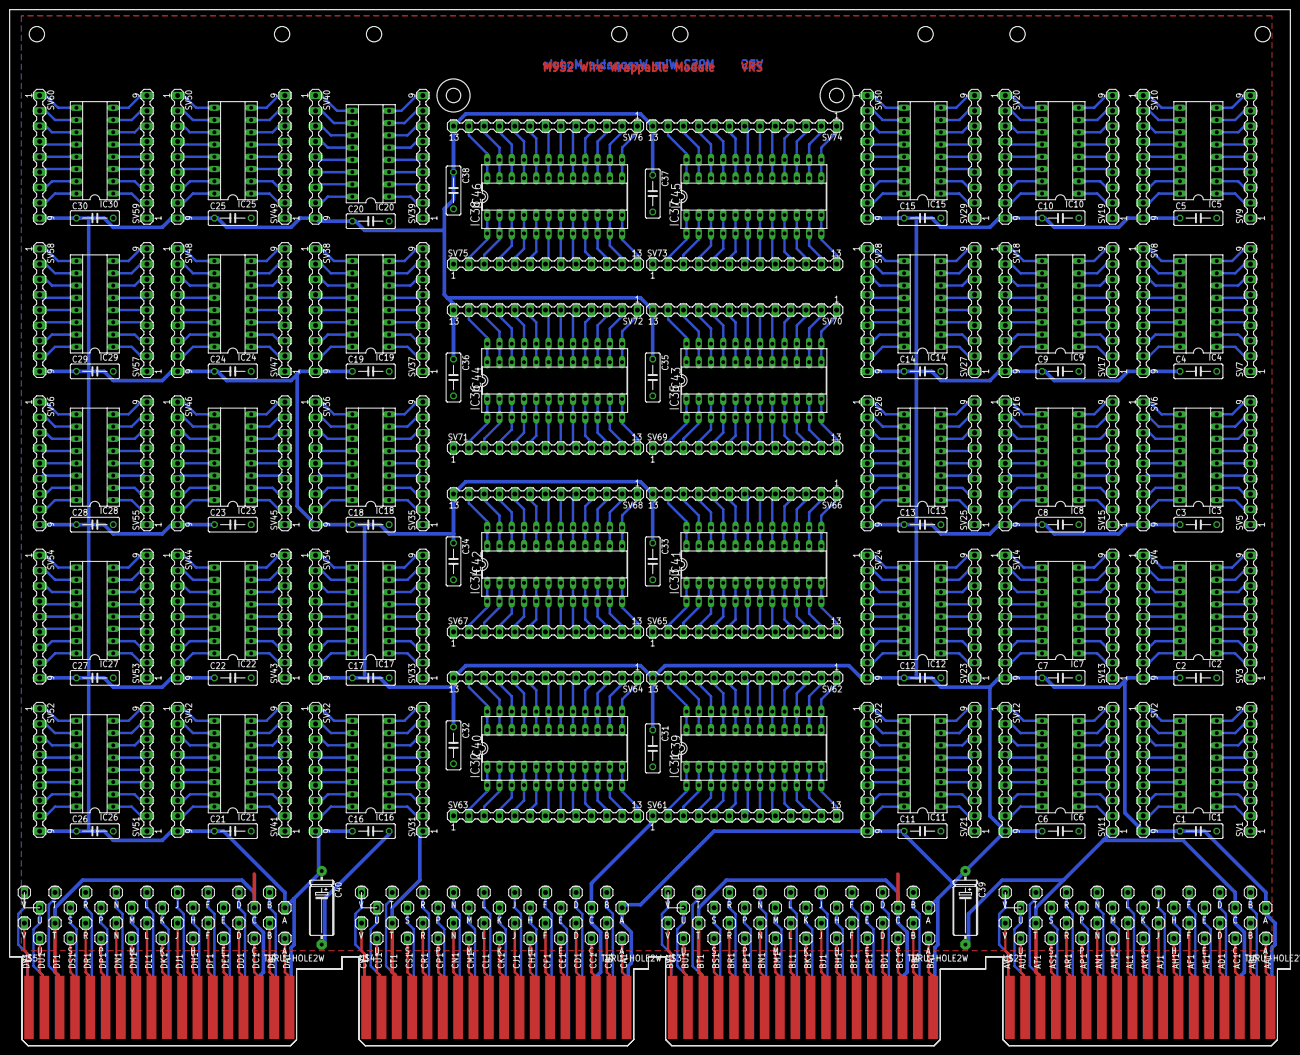
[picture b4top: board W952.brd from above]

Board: 2 copper layers, 265.3 x 214.6 mm, 170 parts (0 on the bottom side), 806 nets.

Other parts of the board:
U$9, U$10: DRIL-3
